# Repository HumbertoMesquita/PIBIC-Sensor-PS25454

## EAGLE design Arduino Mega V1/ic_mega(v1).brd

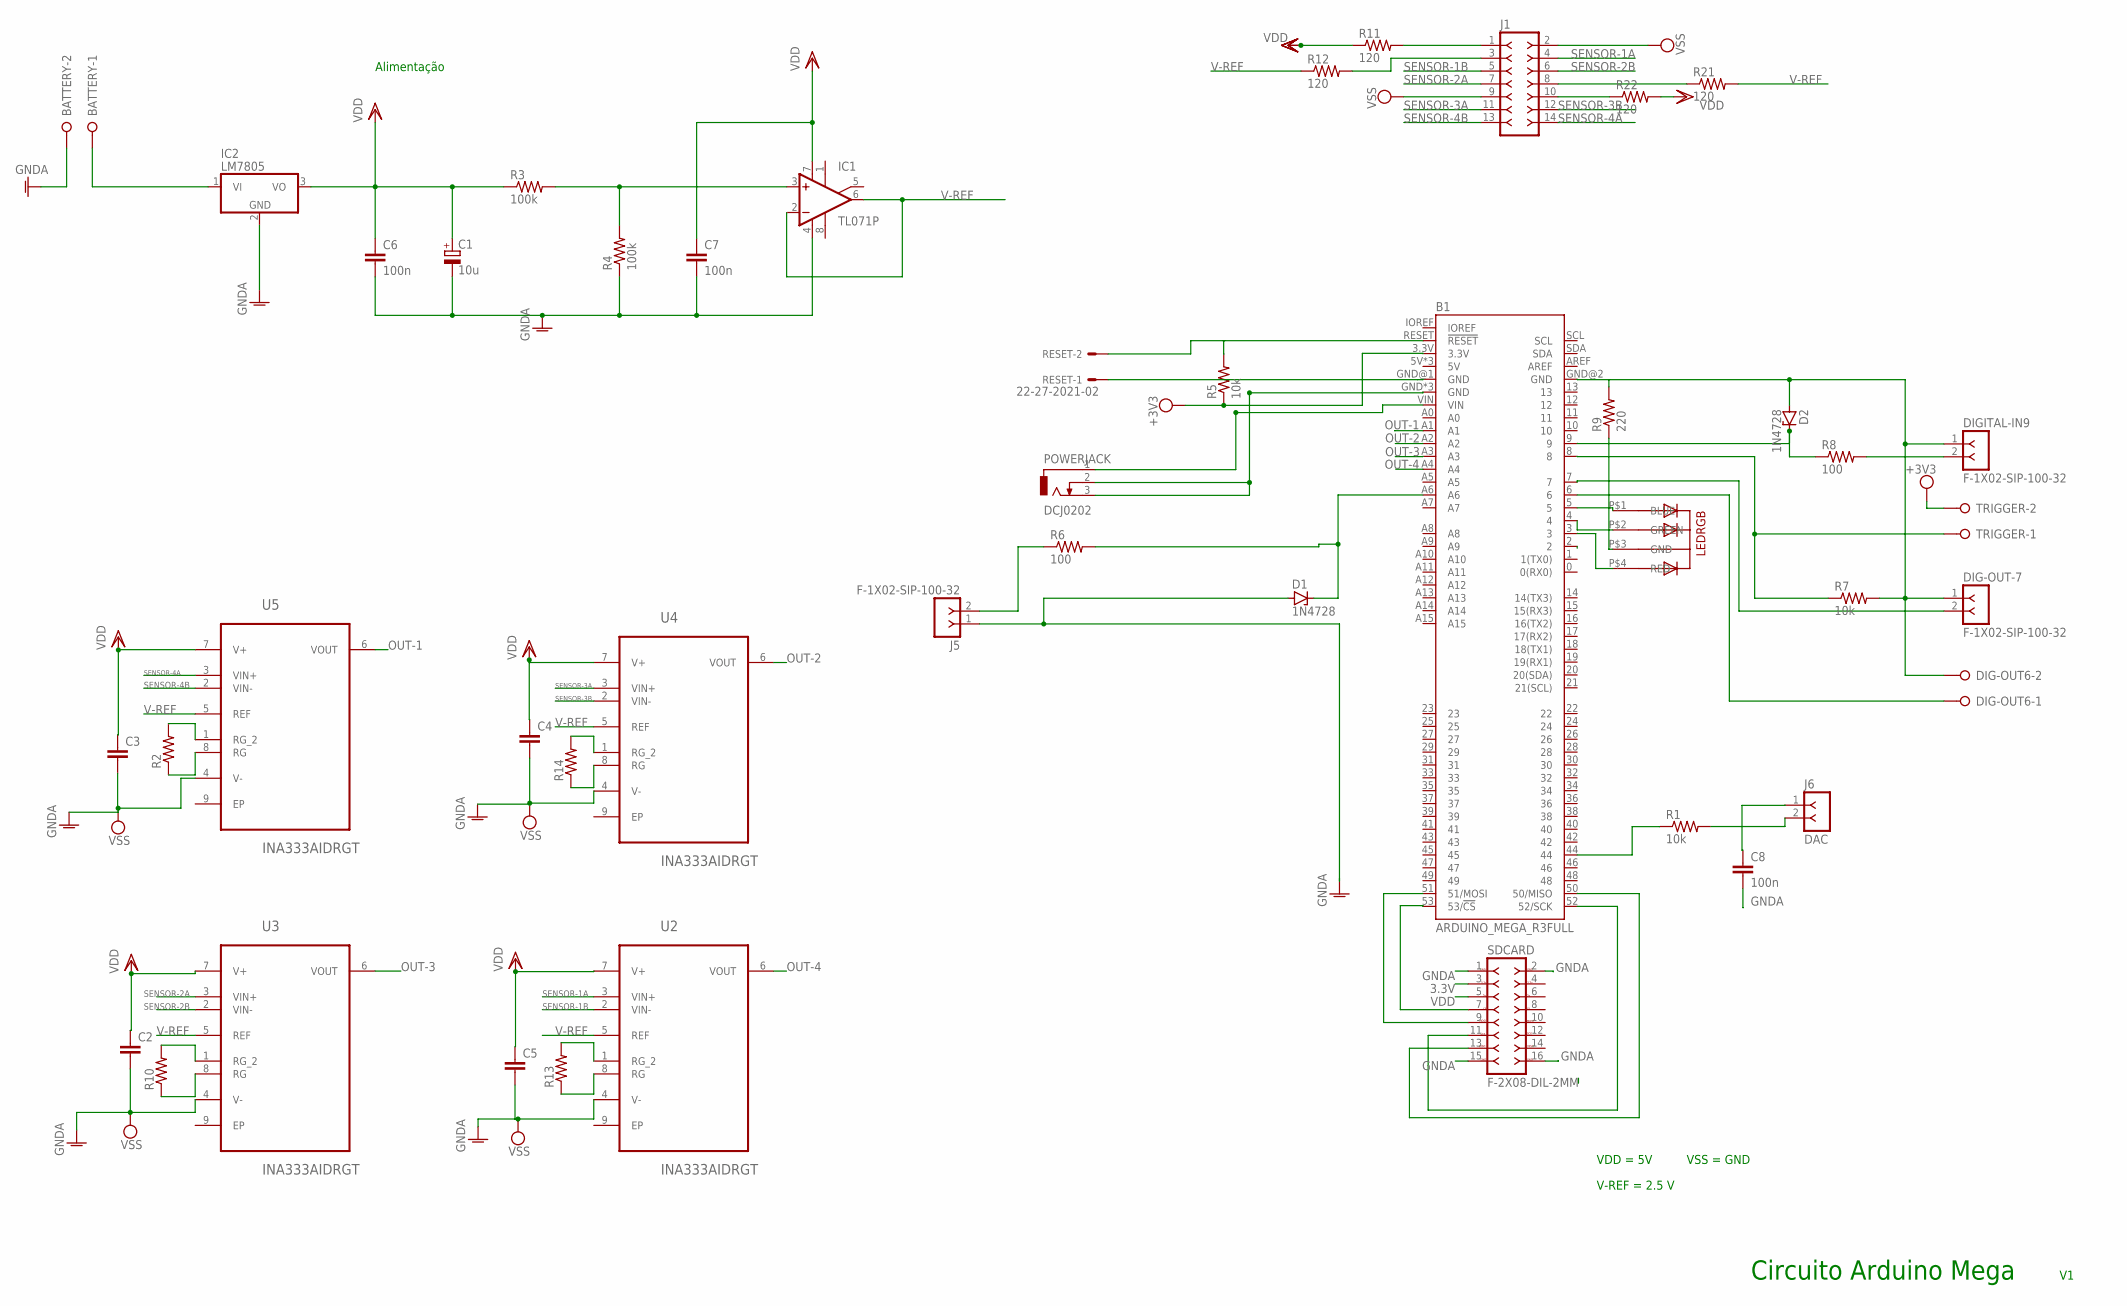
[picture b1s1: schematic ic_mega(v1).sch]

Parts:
B1: ARDUINO_MEGA_R3FULL; ARDUINO_MEGA_NO_SILK
BATTERY: W237-02P; W237-132
C1: 10u; E2,5-7
C2: C-EU050-030X075; C050-030X075
C3, C4, C5: C-EU050-025X075; C050-025X075
C6, C7, C8: 100n; C050-025X075
D1, D2: 1N4728; DO41Z10
DIG-OUT6: W237-02P; W237-132
DIG-OUT-7: F-1X02-SIP-100-32; SIP-100-02-32
DIGITAL-IN9: F-1X02-SIP-100-32; SIP-100-02-32
IC1: TL071P; DIL08
IC2: LM7805; TO220V
J1: F-2X07-79107_M; 79107-14_M
J5: F-1X02-SIP-100-32; SIP-100-02-32
J6: DAC; SIP-100-02-32
LEDRGB: 5MMRGBLED; LED5MMRGB
POWERJACK: DCJ0202
R1, R5, R7: 10k; 0207/10
R2, R10, R13, R14: R-US_0207/10; 0207/10
R3, R4: 100k; 0207/10
R6, R8: 100; 0207/10
R9: 220; 0207/10
R11, R12, R21, R22: 120; 0207/10
RESET: 22-27-2021-02; 6410-02
SDCARD: F-2X08-DIL-2MM; DIL-2MM-2X08
TRIGGER: W237-02P; W237-132
U2, U3, U4, U5: INA333AIDRGT; SON50P300X300X80-9N

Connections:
3.3V: SDCARD.3
unnamed: B1.RESET (!RESET), R5.2, RESET.2
unnamed: BATTERY.1, IC2.1 (VI)
unnamed: LEDRGB.P$3 (GND), R9.1
unnamed: IC1.3 (+IN), R3.2, R4.2
unnamed: B1.A6, D1.C, R6.2
unnamed: B1.5, LEDRGB.P$1 (BLUE)
unnamed: R2.2, U5.1 (RG_2)
unnamed: B1.7, DIG-OUT-7.2
unnamed: B1.51 (51/MOSI), SDCARD.9
unnamed: B1.52 (52/SCK), SDCARD.11
unnamed: B1.6, DIG-OUT6.1
unnamed: B1.9, D2.C, R8.1
unnamed: B1.4, LEDRGB.P$2 (GREEN)
unnamed: R2.1, U5.8 (RG)
unnamed: J1.1, R11.2
unnamed: B1.3, LEDRGB.P$4 (RED)
unnamed: J1.3, R12.2
unnamed: B1.44, R1.1
unnamed: R14.2, U4.1 (RG_2)
unnamed: R14.1, U4.8 (RG)
unnamed: J5.2, R6.1
unnamed: R13.2, U2.1 (RG_2)
unnamed: DIGITAL-IN9.2, R8.2
unnamed: R13.1, U2.8 (RG)
unnamed: B1.53 (53/!CS), SDCARD.7
unnamed: B1.50 (50/MISO), SDCARD.13
unnamed: B1.8, R7.1, TRIGGER.1
unnamed: R10.2, U3.1 (RG_2)
unnamed: R10.1, U3.8 (RG)
unnamed: J1.8, R21.1
unnamed: J1.10, R22.1
unnamed: B1.VIN, POWERJACK.1
unnamed: J6.2, R1.2
unnamed: C8.1, J6.1
OUT-1: B1.A1, U5.6 (VOUT)
OUT-2: B1.A2, U4.6 (VOUT)
OUT-3: B1.A3, U3.6 (VOUT)
OUT-4: B1.A4, U2.6 (VOUT)
SENSOR-1A: J1.4, U2.3 (VIN+)
SENSOR-1B: J1.5, U2.2 (VIN-)
SENSOR-2A: J1.7, U3.3 (VIN+)
SENSOR-2B: J1.6, U3.2 (VIN-)
SENSOR-3A: J1.11, U4.3 (VIN+)
SENSOR-3B: J1.12, U4.2 (VIN-)
SENSOR-4A: J1.14, U5.3 (VIN+)
SENSOR-4B: J1.13, U5.2 (VIN-)
V-REF: IC1.2 (-IN), IC1.6 (OUT), R12.1, R21.2, U2.5 (REF), U3.5 (REF), U4.5 (REF), U5.5 (REF)
VDD: C1.+, C2.1, C3.1, C4.1, C5.1, C6.1, C7.1, IC1.7 (V+), IC2.3 (VO), R3.1, R11.1, R22.2, SDCARD.5, U2.7 (V+), U3.7 (V+), U4.7 (V+), U5.7 (V+)

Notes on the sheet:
Alimentação
VDD = 5V
V-REF = 2.5 V
VSS = GND
Circuito Arduino Mega

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
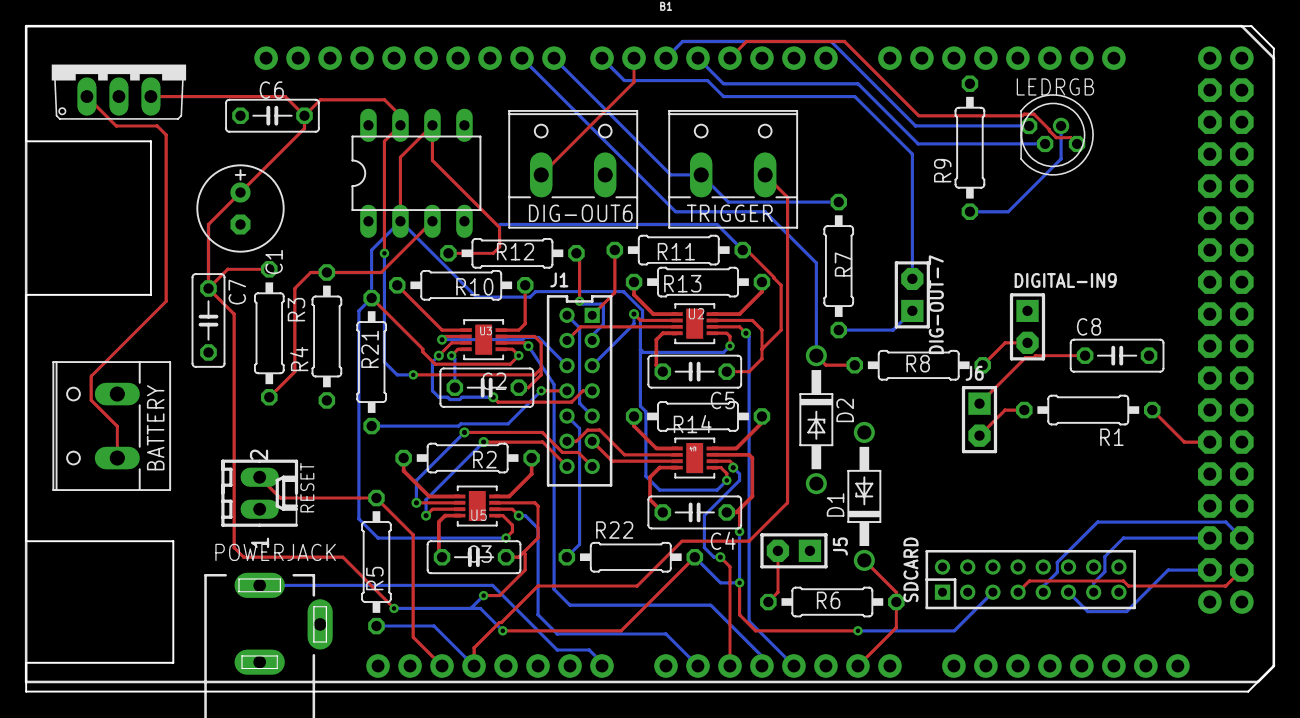
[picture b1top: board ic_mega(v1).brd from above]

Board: 2 copper layers, 99.1 x 52.8 mm, 45 parts (0 on the bottom side), 50 nets.

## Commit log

2024-11-19 versao final 1
2025-02-02 File removed

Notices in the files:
parts and their libraries:
con-headers-jp: Copyright (C) 2008, Bob Starr
SparkFun-Boards: Licensing: Creative Commons ShareAlike 4.0 International - https://creativecommons.org/licenses/by-sa/4.0
